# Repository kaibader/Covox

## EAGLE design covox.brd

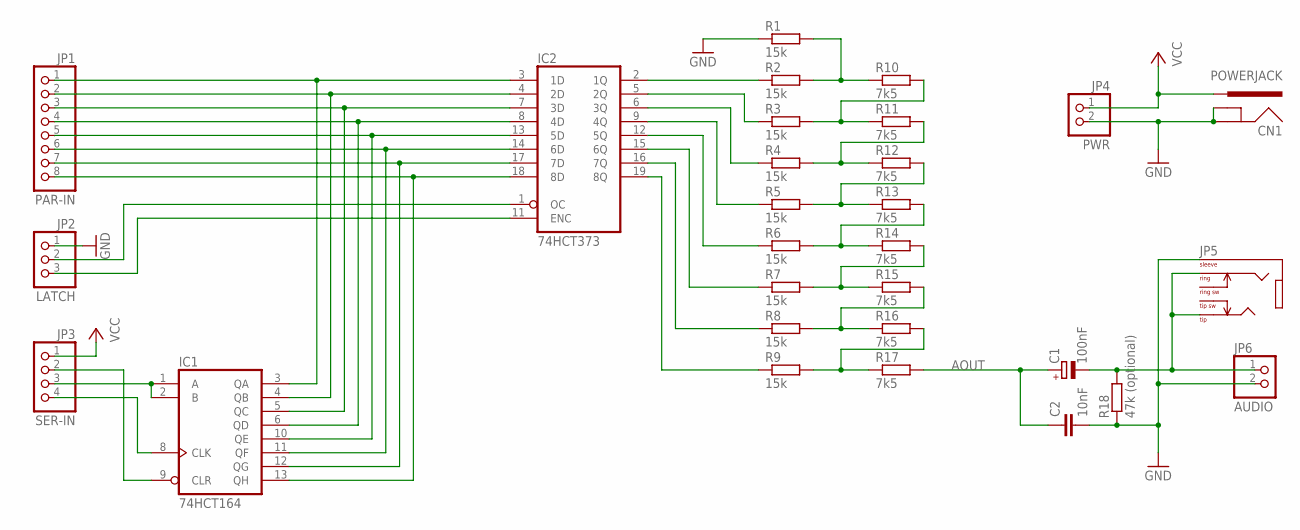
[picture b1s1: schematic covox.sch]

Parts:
C1: 100nF; E2-4
C2: 10nF; C025-025X050
CN1: POWERJACK; POWERJACK_SLOT
IC1: 74HCT164; DIL14
IC2: 74HCT373; DIL20
JP1: PAR-IN; 1X08
JP2: LATCH; 1X03
JP3: SER-IN; 1X04
JP4: PWR; 1X02
JP5: AUDIO; AUDIO-JACK-3.5MM
JP6: AUDIO; 1X02
R1, R2, R3, R4, R5, R6, R7, R8, R9: 15k; 0204/7
R10, R11, R12, R13, R14, R15, R16, R17: 7k5; 0204/7
R18: 47k (optional); 0204/7

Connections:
AOUT: C1.+, C2.1, R17.2
GND: C2.2, CN1.GND@1 (GND), CN1.GND@2 (GND), CN1.GND@3 (GND), CN1.GNDBREAK@1 (GNDBREAK), CN1.GNDBREAK@2 (GNDBREAK), CN1.GNDBREAK@3 (GNDBREAK), IC1.7 (GND), IC2.10 (GND), JP2.1, JP4.2, JP5.1, JP6.2, R1.1, R18.1
unnamed: R1.2, R2.2, R10.1
unnamed: R3.2, R10.2, R11.1
unnamed: R4.2, R11.2, R12.1
unnamed: R5.2, R12.2, R13.1
unnamed: R6.2, R13.2, R14.1
unnamed: R7.2, R14.2, R15.1
unnamed: R8.2, R15.2, R16.1
unnamed: IC2.2 (1Q), R2.1
unnamed: IC2.5 (2Q), R3.1
unnamed: IC2.6 (3Q), R4.1
unnamed: IC2.9 (4Q), R5.1
unnamed: IC2.12 (5Q), R6.1
unnamed: IC2.15 (6Q), R7.1
unnamed: IC2.16 (7Q), R8.1
unnamed: IC2.19 (8Q), R9.1
unnamed: IC1.1 (A), IC1.2 (B), JP3.3
unnamed: R9.2, R16.2, R17.1
unnamed: IC1.3 (QA), IC2.3 (1D), JP1.1
unnamed: IC1.4 (QB), IC2.4 (2D), JP1.2
unnamed: IC1.5 (QC), IC2.7 (3D), JP1.3
unnamed: IC1.6 (QD), IC2.8 (4D), JP1.4
unnamed: IC1.10 (QE), IC2.13 (5D), JP1.5
unnamed: IC1.11 (QF), IC2.14 (6D), JP1.6
unnamed: IC1.12 (QG), IC2.17 (7D), JP1.7
unnamed: IC1.13 (QH), IC2.18 (8D), JP1.8
unnamed: IC2.1 (OC), JP2.2
unnamed: IC2.11 (ENC), JP2.3
unnamed: IC1.9 (CLR), JP3.2
unnamed: IC1.8 (CLK), JP3.4
unnamed: C1.-, JP5.2, JP5.3, JP6.1, R18.2
VCC: CN1.PWR@1 (PWR), CN1.PWR@2 (PWR), CN1.PWR@3 (PWR), IC1.14 (VCC), IC2.20 (VCC), JP3.1, JP4.1

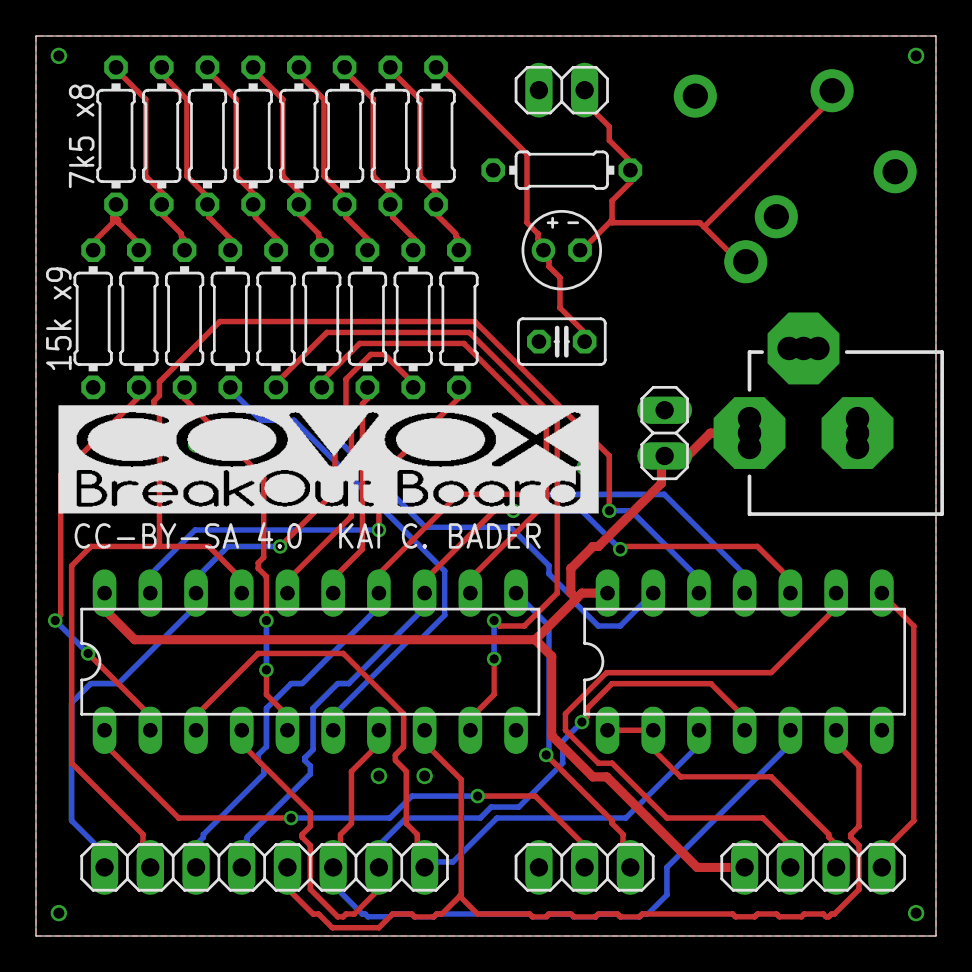
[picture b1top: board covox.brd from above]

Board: 2 copper layers, 50.0 x 50.0 mm, 30 parts (0 on the bottom side), 33 nets.

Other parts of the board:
U$2: COVOX_LOGO_600

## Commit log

2015-05-20 Initial commit. Work in progress...
2015-05-20 Updates...
2015-05-25 Generated Covox Gerber files.
2017-06-10 Ported design files from EagleCAD to KiCad.
    This was a test of the Eagle-to-KiCad toolset to port a whole project from
    EagleCAD to KiCad. The resulting board file is currently broken due to
    copper fill settings between the two design tools.
2017-06-10 Moved EagleCAD files into a separate directory

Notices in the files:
covox.brd:
CC-BY-SA 4.0  KAI C. BADER
